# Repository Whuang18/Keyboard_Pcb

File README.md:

This is a readme of my project PCB. To be filled out when I am completed.

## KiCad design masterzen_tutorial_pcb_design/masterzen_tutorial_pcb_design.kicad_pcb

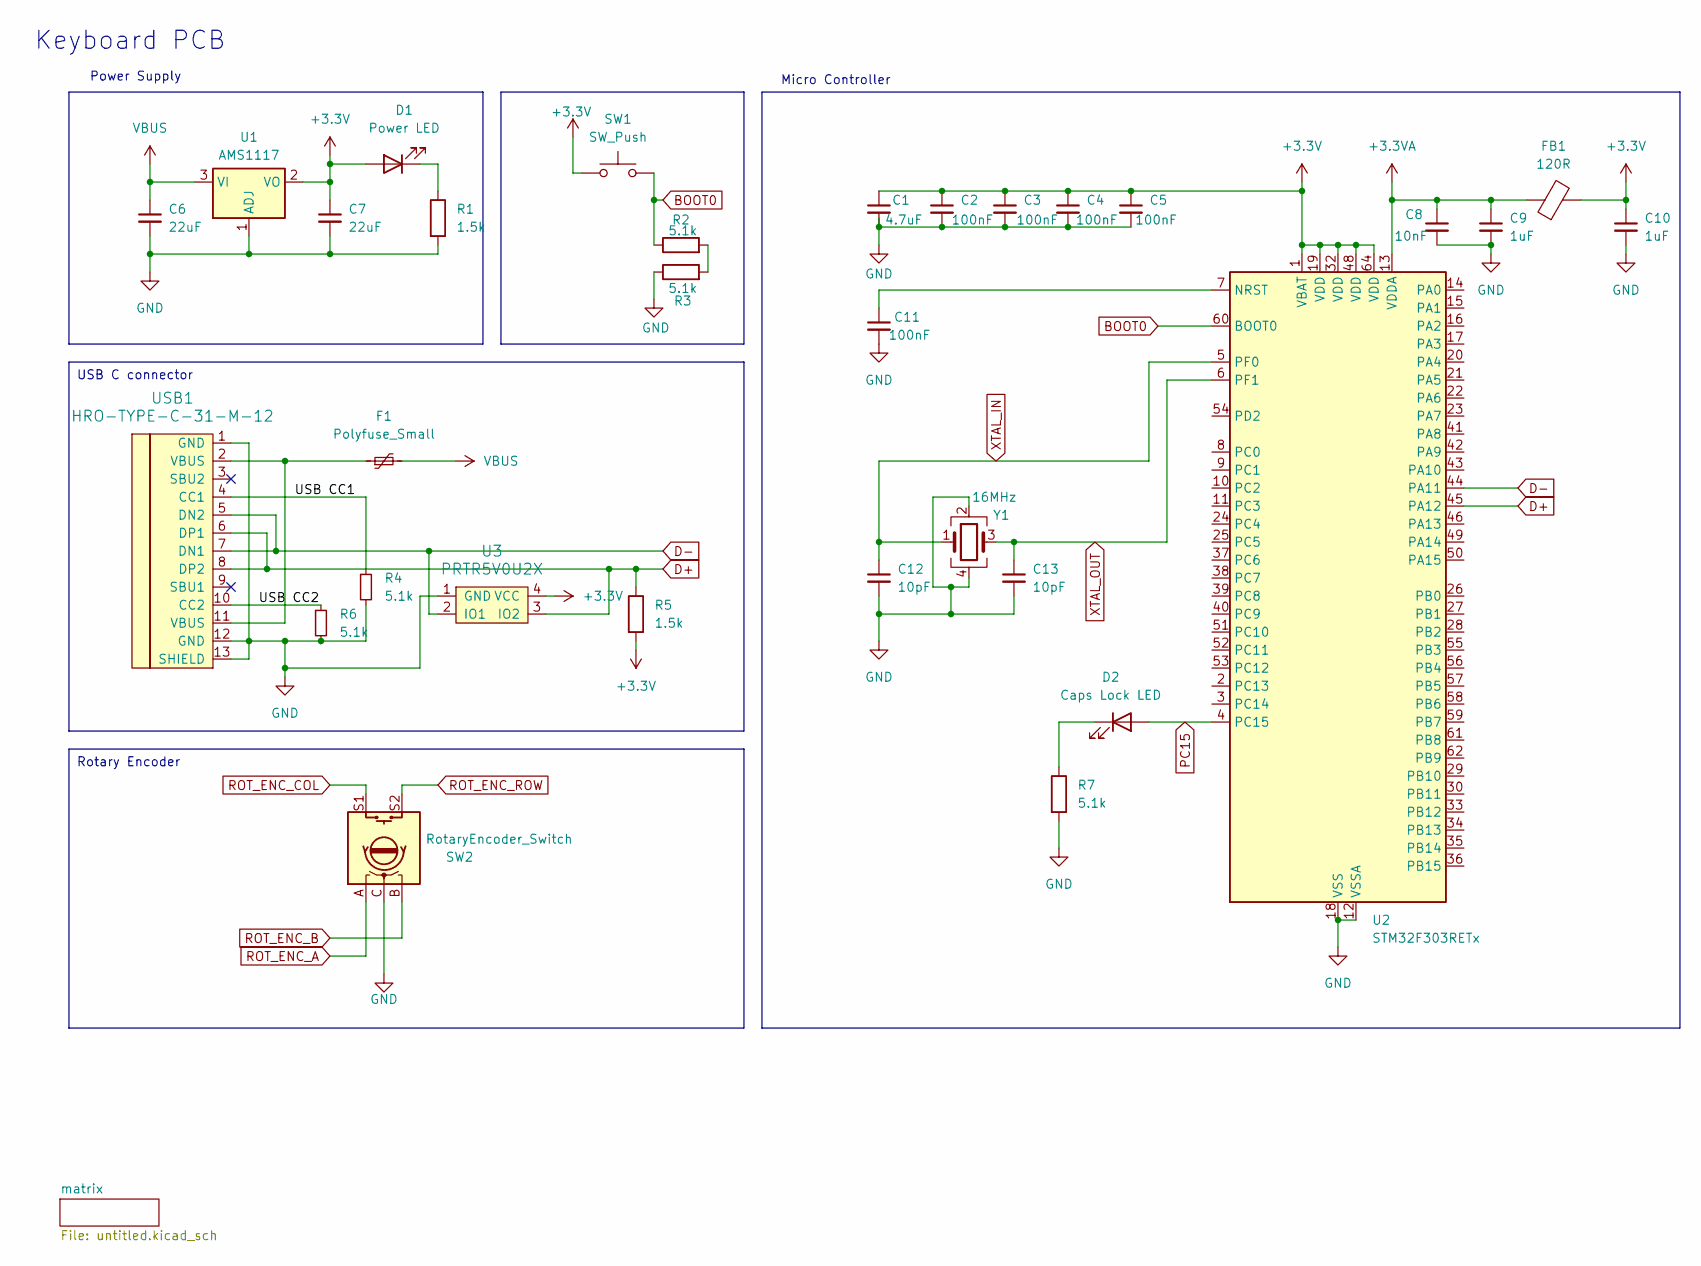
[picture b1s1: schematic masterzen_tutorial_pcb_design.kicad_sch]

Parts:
C1: 4.7uF; C_0805_2012Metric_Pad1.18x1.45mm_HandSolder
C2, C3, C4, C5, C11: 100nF; C_0805_2012Metric_Pad1.18x1.45mm_HandSolder
C6, C7: 22uF; C_0805_2012Metric_Pad1.18x1.45mm_HandSolder
C8: 10nF; C_0805_2012Metric_Pad1.18x1.45mm_HandSolder
C9, C10: 1uF; C_0805_2012Metric_Pad1.18x1.45mm_HandSolder
C12, C13: 10pF; C_0805_2012Metric_Pad1.18x1.45mm_HandSolder
D1: Power LED; LED_0201_0603Metric_Pad0.64x0.40mm_HandSolder
D2: Caps Lock LED; LED_0805_2012Metric_Pad1.15x1.40mm_HandSolder
F1: Polyfuse_Small; L_0603_1608Metric
FB1: 120R; L_0603_1608Metric
R1, R5: 1.5k; R_0805_2012Metric_Pad1.20x1.40mm_HandSolder
R2, R3, R4, R6, R7: 5.1k; R_0805_2012Metric_Pad1.20x1.40mm_HandSolder
SW1: SW_Push; SW_SPST_SKQG_WithStem
SW2: RotaryEncoder_Switch; RotaryEncoder_Alps_EC11E-Switch_Vertical_H20mm_CircularMoun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
U1: AMS1117; SOT-223-3_TabPin2
U2: STM32F303RETx; LQFP-64_10x10mm_P0.5mm
U3: PRTR5V0U2X; SOT143B
USB1: HRO-TYPE-C-31-M-12; HRO-TYPE-C-31-M-12-HandSoldering
Y1: 16MHz; Crystal_SMD_3225-4Pin_3.2x2.5mm

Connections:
+3.3V: C1.1, C2.1, C3.1, C4.1, C5.1, C7.1, C10.1, D1.2 (A), FB1.2, R5.2, SW1.1, U1.2 (VO), U2.1 (VBAT), U2.19 (VDD), U2.32 (VDD), U2.48 (VDD), U2.64 (VDD), U3.4 (VCC)
+3.3VA: C8.1, C9.1, FB1.1, U2.13 (VDDA)
/USB CC1: R4.1, USB1.4 (CC1)
/USB CC2: R6.1, USB1.10 (CC2)
BOOT0: R2.1, SW1.2, U2.60 (BOOT0); also elsewhere on the board
D+: R5.1, U2.45 (PA12), U3.3 (IO2), USB1.6 (DP1), USB1.8 (DP2)
D-: U2.44 (PA11), U3.2 (IO1), USB1.5 (DN2), USB1.7 (DN1)
GND: C1.2, C2.2, C3.2, C4.2, C5.2, C6.2, C7.2, C8.2, C9.2, C10.2, C11.2, C12.2, C13.2, R1.2, R3.1, R4.2, R6.2, R7.2, SW2.C, U1.1 (ADJ), U2.12 (VSSA), U2.18 (VSS), U2.31 (VSS), U2.47 (VSS), U2.63 (VSS), U3.1 (GND), USB1.1 (GND), USB1.12 (GND), USB1.13 (SHIELD), Y1.2, Y1.4; also elsewhere on the board
unnamed: D1.1 (K), R1.1
unnamed: D2.1 (K), R7.1
unnamed: F1.1, USB1.2 (VBUS), USB1.11 (VBUS)
unnamed: R2.2, R3.2
unnamed: C11.1, U2.7 (NRST)
PC15: D2.2 (A), U2.4 (PC15)
ROT_ENC_A: SW2.A
ROT_ENC_B: SW2.B
ROT_ENC_COL: SW2.S1; also elsewhere on the board
ROT_ENC_ROW: SW2.S2; also elsewhere on the board
VBUS: C6.1, F1.2, U1.3 (VI)
XTAL_IN: C12.1, U2.5 (PF0), Y1.1
XTAL_OUT: C13.1, U2.6 (PF1), Y1.3

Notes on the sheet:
USB C connector
Rotary Encoder
Micro Controller
Keyboard PCB
Power Supply

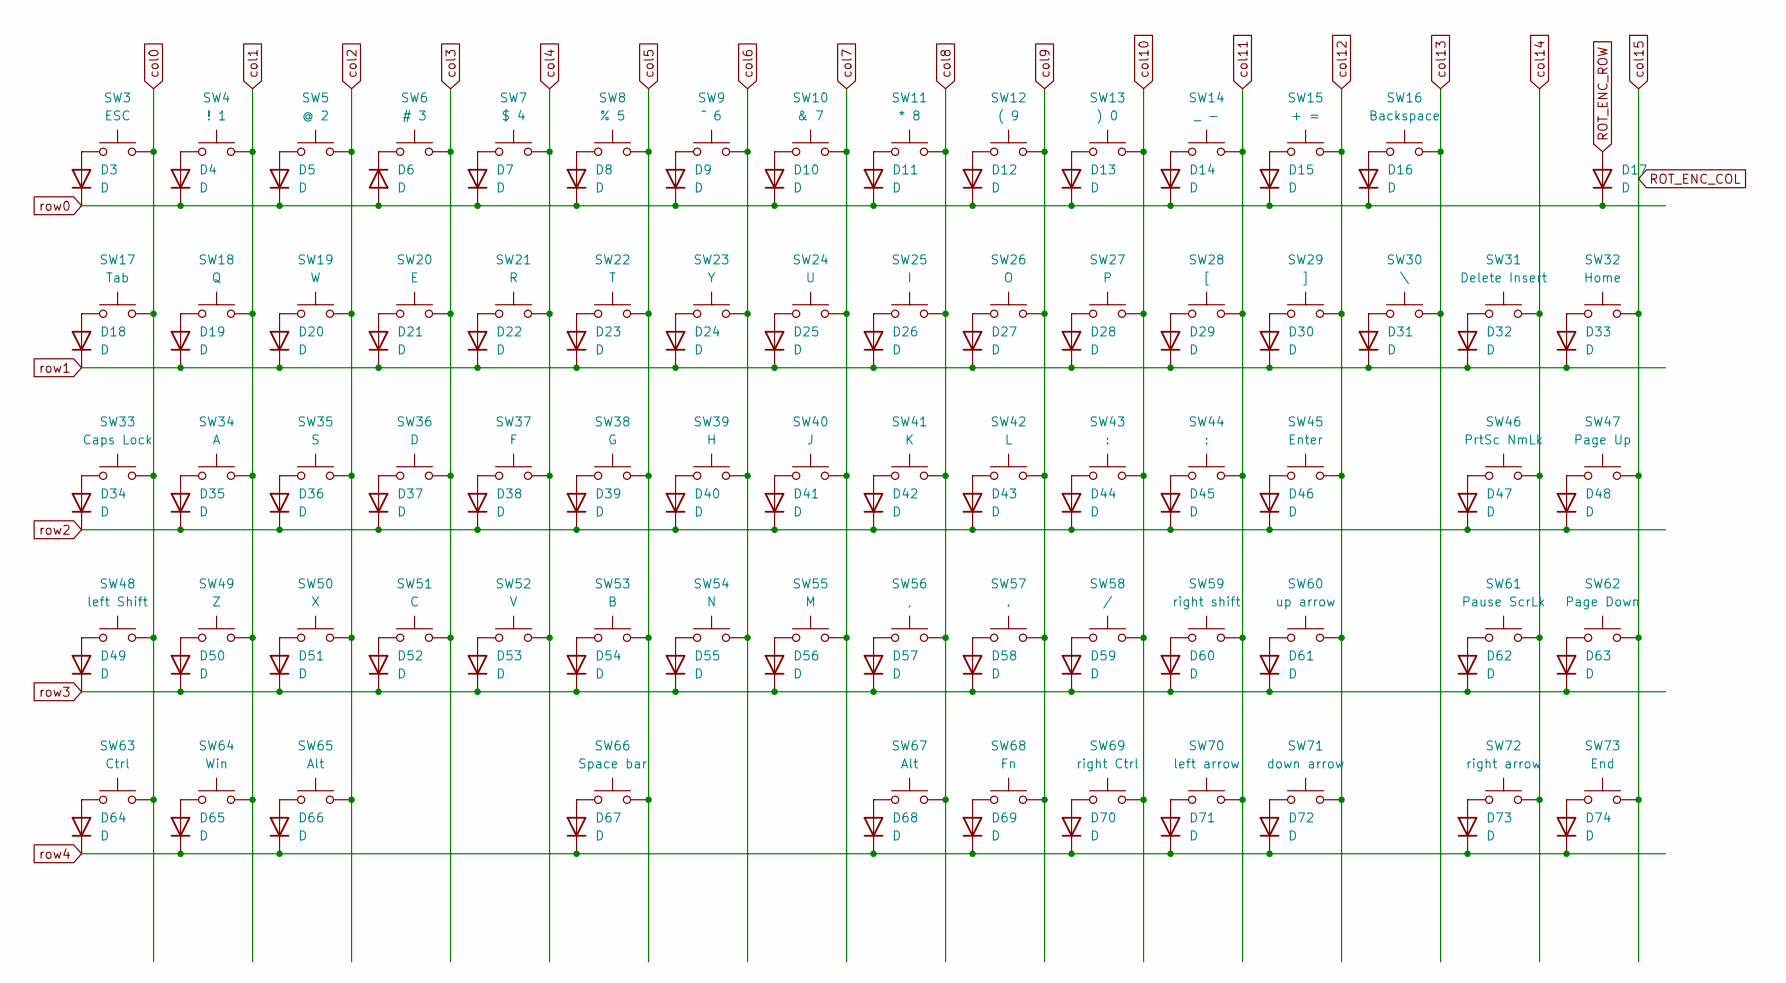
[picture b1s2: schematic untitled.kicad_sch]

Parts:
D3, D4, D5, D6, D7, D8, D9, D10, D11, D12, D13, D14, D15, D16, D17, D18, D19, D20, D21, D22, D23, D24, D25, D26, D27, D28, D29, D30, D31, D32, D33, D34, D35, D36, D37, D38, D39, D40, D41, D42, D43, D44, D45, D46, D47, D48, D49, D50, D51, D52, D53, D54, D55, D56, D57, D58, D59, D60, D61, D62, D63, D64, D65, D66, D67, D68, D69, D70, D71, D72, D73, D74: D; D_SOD-123
SW3: ESC; MXOnly-1U-NoLED
SW4: ! 1; MXOnly-1U-NoLED
SW5: @ 2; MXOnly-1U-NoLED
SW6: # 3; MXOnly-1U-NoLED
SW7: $ 4; MXOnly-1U-NoLED
SW8: % 5; MXOnly-1U-NoLED
SW9: ^ 6; MXOnly-1U-NoLED
SW10: & 7; MXOnly-1U-NoLED
SW11: * 8; MXOnly-1U-NoLED
SW12: ( 9; MXOnly-1U-NoLED
SW13: ) 0; MXOnly-1U-NoLED
SW14: _ -; MXOnly-1U-NoLED
SW15: + =; MXOnly-1U-NoLED
SW16: Backspace; MXOnly-2U-NoLED
SW17: Tab; MXOnly-1.5U-NoLED
SW18: Q; MXOnly-1U-NoLED
SW19: W; MXOnly-1U-NoLED
SW20: E; MXOnly-1U-NoLED
SW21: R; MXOnly-1U-NoLED
SW22: T; MXOnly-1U-NoLED
SW23: Y; MXOnly-1U-NoLED
SW24: U; MXOnly-1U-NoLED
SW25: I; MXOnly-1U-NoLED
SW26: O; MXOnly-1U-NoLED
SW27: P; MXOnly-1U-NoLED
SW28: [; MXOnly-1U-NoLED
SW29: ]; MXOnly-1U-NoLED
SW30: \; MXOnly-1.5U-NoLED
SW31: Delete Insert; MXOnly-1U-NoLED
SW32: Home; MXOnly-1U-NoLED
SW33: Caps Lock; MXOnly-1.75U-NoLED
SW34: A; MXOnly-1U-NoLED
SW35: S; MXOnly-1U-NoLED
SW36: D; MXOnly-1U-NoLED
SW37: F; MXOnly-1U-NoLED
SW38: G; MXOnly-1U-NoLED
SW39: H; MXOnly-1U-NoLED
SW40: J; MXOnly-1U-NoLED
SW41: K; MXOnly-1U-NoLED
SW42: L; MXOnly-1U-NoLED
SW43, SW44: :; MXOnly-1U-NoLED
SW45: Enter; MXOnly-2.25U-NoLED
SW46: PrtSc NmLk; MXOnly-1U-NoLED
SW47: Page Up; MXOnly-1U-NoLED
SW48: left Shift; MXOnly-2.25U-NoLED
SW49: Z; MXOnly-1U-NoLED
SW50: X; MXOnly-1U-NoLED
SW51: C; MXOnly-1U-NoLED
SW52: V; MXOnly-1U-NoLED
SW53: B; MXOnly-1U-NoLED
SW54: N; MXOnly-1U-NoLED
SW55: M; MXOnly-1U-NoLED
SW56: ,; MXOnly-1U-NoLED
SW57: .; MXOnly-1U-NoLED
SW58: /; MXOnly-1U-NoLED
SW59: right shift; MXOnly-1.75U-NoLED
SW60: up arrow; MXOnly-1U-NoLED
SW61: Pause ScrLk; MXOnly-1U-NoLED
SW62: Page Down; MXOnly-1U-NoLED
SW63: Ctrl; MXOnly-1.25U-NoLED
SW64: Win; MXOnly-1.25U-NoLED
SW65: Alt; MXOnly-1.25U-NoLED
SW66: Space bar; MXOnly-6.25U-NoLED
SW67: Alt; MXOnly-1U-NoLED
SW68: Fn; MXOnly-1U-NoLED
SW69: right Ctrl; MXOnly-1U-NoLED
SW70: left arrow; MXOnly-1U-NoLED
SW71: down arrow; MXOnly-1U-NoLED
SW72: right arrow; MXOnly-1U-NoLED
SW73: End; MXOnly-1U-NoLED

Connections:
unnamed: D3.2 (A), SW3.1
unnamed: D4.2 (A), SW4.1
unnamed: D5.2 (A), SW5.1
unnamed: D6.1 (K), SW6.1
unnamed: D7.2 (A), SW7.1
unnamed: D8.2 (A), SW8.1
unnamed: D9.2 (A), SW9.1
unnamed: D10.2 (A), SW10.1
unnamed: D11.2 (A), SW11.1
unnamed: D12.2 (A), SW12.1
unnamed: D13.2 (A), SW13.1
unnamed: D14.2 (A), SW14.1
unnamed: D15.2 (A), SW15.1
unnamed: D16.2 (A), SW16.1
unnamed: D18.2 (A), SW17.1
unnamed: D19.2 (A), SW18.1
unnamed: D20.2 (A), SW19.1
unnamed: D21.2 (A), SW20.1
unnamed: D22.2 (A), SW21.1
unnamed: D23.2 (A), SW22.1
unnamed: D24.2 (A), SW23.1
unnamed: D25.2 (A), SW24.1
unnamed: D26.2 (A), SW25.1
unnamed: D27.2 (A), SW26.1
unnamed: D28.2 (A), SW27.1
unnamed: D29.2 (A), SW28.1
unnamed: D30.2 (A), SW29.1
unnamed: D31.2 (A), SW30.1
unnamed: D32.2 (A), SW31.1
unnamed: D33.2 (A), SW32.1
unnamed: D34.2 (A), SW33.1
unnamed: D35.2 (A), SW34.1
unnamed: D36.2 (A), SW35.1
unnamed: D37.2 (A), SW36.1
unnamed: D38.2 (A), SW37.1
unnamed: D39.2 (A), SW38.1
unnamed: D40.2 (A), SW39.1
unnamed: D41.2 (A), SW40.1
unnamed: D42.2 (A), SW41.1
unnamed: D43.2 (A), SW42.1
unnamed: D44.2 (A), SW43.1
unnamed: D45.2 (A), SW44.1
unnamed: D46.2 (A), SW45.1
unnamed: D47.2 (A), SW46.1
unnamed: D48.2 (A), SW47.1
unnamed: D49.2 (A), SW48.1
unnamed: D50.2 (A), SW49.1
unnamed: D51.2 (A), SW50.1
unnamed: D52.2 (A), SW51.1
unnamed: D53.2 (A), SW52.1
unnamed: D54.2 (A), SW53.1
unnamed: D55.2 (A), SW54.1
unnamed: D56.2 (A), SW55.1
unnamed: D57.2 (A), SW56.1
unnamed: D58.2 (A), SW57.1
unnamed: D59.2 (A), SW58.1
unnamed: D60.2 (A), SW59.1
unnamed: D61.2 (A), SW60.1
unnamed: D62.2 (A), SW61.1
unnamed: D63.2 (A), SW62.1
unnamed: D64.2 (A), SW63.1
unnamed: D65.2 (A), SW64.1
unnamed: D66.2 (A), SW65.1
unnamed: D67.2 (A), SW66.1
unnamed: D68.2 (A), SW67.1
unnamed: D69.2 (A), SW68.1
unnamed: D70.2 (A), SW69.1
unnamed: D71.2 (A), SW70.1
unnamed: D72.2 (A), SW71.1
unnamed: D73.2 (A), SW72.1
unnamed: D74.2 (A), SW73.1
ROT_ENC_COL: SW32.2, SW47.2, SW62.2, SW73.2; also elsewhere on the board
ROT_ENC_ROW: D17.2 (A); also elsewhere on the board
col0: SW3.2, SW17.2, SW33.2, SW48.2, SW63.2
col1: SW4.2, SW18.2, SW34.2, SW49.2, SW64.2
col2: SW5.2, SW19.2, SW35.2, SW50.2, SW65.2
col3: SW6.2, SW20.2, SW36.2, SW51.2
col4: SW7.2, SW21.2, SW37.2, SW52.2
col5: SW8.2, SW22.2, SW38.2, SW53.2, SW66.2
col6: SW9.2, SW23.2, SW39.2, SW54.2
col7: SW10.2, SW24.2, SW40.2, SW55.2
col8: SW11.2, SW25.2, SW41.2, SW56.2, SW67.2
col9: SW12.2, SW26.2, SW42.2, SW57.2, SW68.2
col10: SW13.2, SW27.2, SW43.2, SW58.2, SW69.2
col11: SW14.2, SW28.2, SW44.2, SW59.2, SW70.2
col12: SW15.2, SW29.2, SW45.2, SW60.2, SW71.2
col13: SW16.2, SW30.2
col14: SW31.2, SW46.2, SW61.2, SW72.2
row0: D3.1 (K), D4.1 (K), D5.1 (K), D6.2 (A), D7.1 (K), D8.1 (K), D9.1 (K), D10.1 (K), D11.1 (K), D12.1 (K), D13.1 (K), D14.1 (K), D15.1 (K), D16.1 (K), D17.1 (K)
row1: D18.1 (K), D19.1 (K), D20.1 (K), D21.1 (K), D22.1 (K), D23.1 (K), D24.1 (K), D25.1 (K), D26.1 (K), D27.1 (K), D28.1 (K), D29.1 (K), D30.1 (K), D31.1 (K), D32.1 (K), D33.1 (K)
row2: D34.1 (K), D35.1 (K), D36.1 (K), D37.1 (K), D38.1 (K), D39.1 (K), D40.1 (K), D41.1 (K), D42.1 (K), D43.1 (K), D44.1 (K), D45.1 (K), D46.1 (K), D47.1 (K), D48.1 (K)
row3: D49.1 (K), D50.1 (K), D51.1 (K), D52.1 (K), D53.1 (K), D54.1 (K), D55.1 (K), D56.1 (K), D57.1 (K), D58.1 (K), D59.1 (K), D60.1 (K), D61.1 (K), D62.1 (K), D63.1 (K)
row4: D64.1 (K), D65.1 (K), D66.1 (K), D67.1 (K), D68.1 (K), D69.1 (K), D70.1 (K), D71.1 (K), D72.1 (K), D73.1 (K), D74.1 (K)

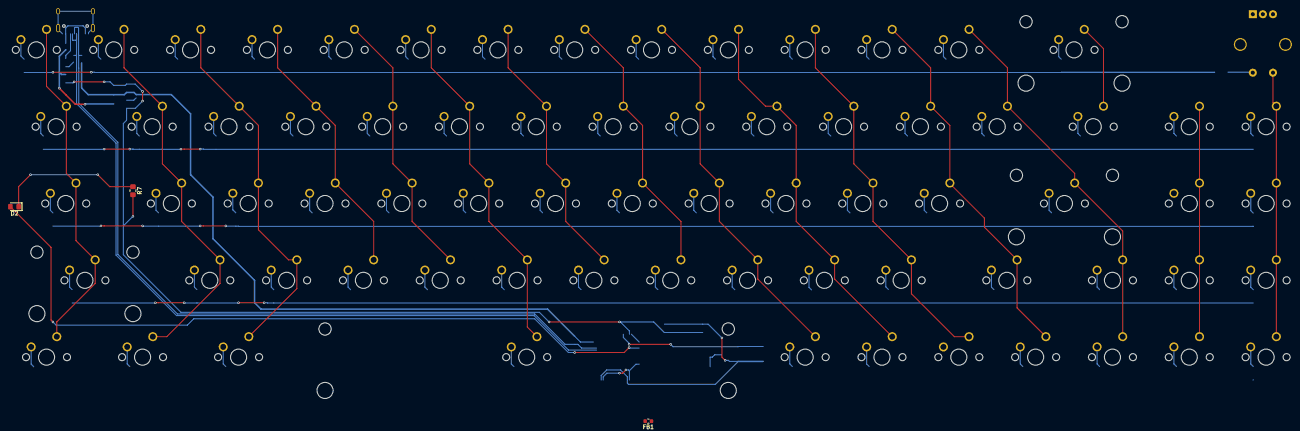
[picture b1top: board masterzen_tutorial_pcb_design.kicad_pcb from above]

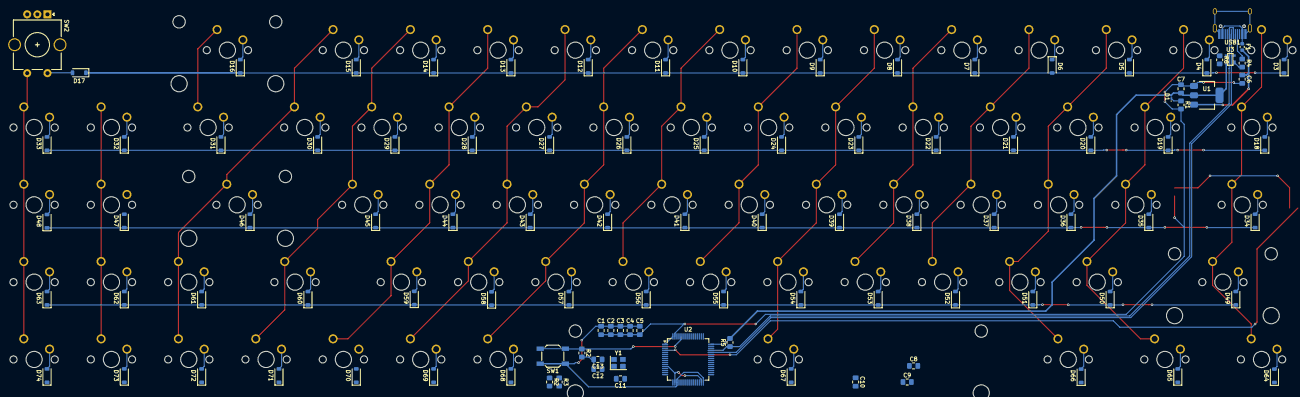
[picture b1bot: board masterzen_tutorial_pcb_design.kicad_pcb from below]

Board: 2 copper layers, 175 parts (101 on the bottom side), 110 nets.

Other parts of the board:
R2#2: 10k; R_0805_2012Metric_Pad1.20x1.40mm_HandSolder

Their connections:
BOOT0: R2#2.1; also elsewhere on the board
GND: R2#2.2; also elsewhere on the board

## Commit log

2024-08-11 added aio's libraries
2024-08-12 initial commit for pcb design
2024-08-12 removed the autosaved files and opened files
2024-08-12 moved submodules and added reeset button
2024-08-12 updated file path for submodules
2024-08-12 removed submodules so I can readd them
2024-08-12 added submodules
2024-08-12 added gitignore
2024-08-13 added connected some of the USB lines
2024-08-13 added d+ and d- to usb header
2024-08-17 finished part 1
2024-08-19 initial matrix
2024-11-11 Updated Schematic with correct keys
2025-01-13 switched micro to the STM32F303
2025-01-13 updated gitignore
2025-01-13 minor changes to schematic
2025-01-14 replaced polyfuse with ferrite bead
2025-01-21 finished schematic
2025-01-22 starting placing components on a pcb
2025-01-22 routed matrix
